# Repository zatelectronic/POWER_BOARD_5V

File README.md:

<div align="center">

# POWER BOARD +5V

**Placa de alimentação DC-DC step-down (buck converter) com entrada de 24V e saída regulada de 5V, baseada em regulador chaveado SMD de alta eficiência**

</div>

---

## 📋 Índice

- [POWER BOARD +5V](#power-board-5v)
  - [📋 Índice](#-índice)
  - [Visão Geral](#visão-geral)
  - [Renders 3D](#renders-3d)
  - [Funcionalidades](#funcionalidades)
  - [Diagrama de Funcionamento](#diagrama-de-funcionamento)
  - [Especificações Técnicas](#especificações-técnicas)
  - [Lista de Materiais](#lista-de-materiais)
  - [Pinagem dos Conectores](#pinagem-dos-conectores)
    - [DC IN — Entrada (lado esquerdo)](#dc-in--entrada-lado-esquerdo)
    - [DC OUT — Saída (lado direito)](#dc-out--saída-lado-direito)
    - [Pontos de Teste](#pontos-de-teste)
  - [Aplicações](#aplicações)
  - [Estrutura do Repositório](#estrutura-do-repositório)
  - [Como Usar](#como-usar)
    - [Instalação básica](#instalação-básica)
    - [Dica de Integração](#dica-de-integração)
  - [⚠️ Avisos de Segurança](#️-avisos-de-segurança)
  - [Sobre](#sobre)

---

## Visão Geral

**POWER BOARD +5V** é uma placa de alimentação DC-DC do tipo **buck converter (step-down)**, projetada pela **ZAT ELECTRONIC** utilizando **KiCad 10**. A placa converte uma tensão de entrada de **+24VDC** em uma saída regulada e estável de **+5VDC / 3A**, utilizando o regulador chaveado **LM2596S-5** no encapsulamento TO-263-5 (SMD).

O design é compacto e totalmente SMD, com conexões de entrada e saída por **pads de solda** expostos diretamente na PCB. A placa inclui **fusível de proteção SMD 3A**, **diodo Schottky** de roda livre, **indutor de 33µH** e capacitores eletrolíticos de alta capacidade para filtragem e estabilidade da saída.

> ⚡ Topologia **buck converter** de alta eficiência — ideal para sistemas embarcados, painéis de controle industrial e projetos que alimentam microcontroladores e periféricos a partir de fontes de 24VDC.

---

## Renders 3D

<div align="center">

*Vista superior — regulador LM2596S-5, indutor, capacitores eletrolíticos e fusível SMD*

<br/>

*Vista isométrica — layout compacto com pads DC IN e DC OUT nas extremidades*

</div>

---

## Funcionalidades

- ✅ **Regulador chaveado LM2596S-5** (TO-263-5 SMD) — saída fixa de 5V, até 3A
- ✅ **Topologia buck converter** — alta eficiência em comparação com reguladores lineares
- ✅ **Entrada 24VDC** — compatível com fontes industriais e painéis de automação
- ✅ **Saída 5VDC / 3A** — alimentação estável para microcontroladores e periféricos
- ✅ **Fusível SMD 3A** (encapsulamento 1808/2410) — proteção contra sobrecorrente na entrada
- ✅ **Diodo Schottky SS54** (SMA SMD) — diodo de roda livre de alta velocidade
- ✅ **Indutor 33µH** (12×12mm) — núcleo de potência para o estágio de conversão
- ✅ **Capacitor de entrada 100µF/35V** (SMD eletrolítico) — filtragem da tensão de entrada
- ✅ **Capacitor de saída 680µF/16V** (SMD eletrolítico) — filtragem e estabilidade da saída
- ✅ **4 pontos de teste (TP1–TP4)** — facilidade de medição e diagnóstico em bancada
- ✅ **Pads de conexão expostos** — DC IN (+24V / GND) e DC OUT (+5V / GND)
- ✅ **Layout totalmente SMD** — compacto e adequado para integração em painéis

---

## Diagrama de Funcionamento

```
DC IN (+24V) ──[F1 3A]──[D1 SMA]──────────────────────► +24V interno
                                   │
                                  [C5 100µF/35V] (filtro entrada)
                                   │
                              [U2 LM2596S-5]  ← Regulador buck
                                   │
                                  [L1 33µH]   ← Indutor de saída
                                   │
                    [D2 SS54] ←────┤            ← Diodo Schottky (roda livre)
                    (SMA SMD)      │
                                  [C6 680µF/16V] (filtro saída)
                                   │
DC OUT (+5V) ◄─────────────────────┘

DC IN (GND) ──────────────────────────────────────────► DC OUT (GND)

TP1, TP2 → pontos de teste na entrada
TP3, TP4 → pontos de teste na saída
```

---

## Especificações Técnicas

| Parâmetro | Valor |
|-----------|-------|
| **Topologia** | Buck Converter (Step-Down) |
| **Regulador** | LM2596S-5 (TO-263-5 SMD) |
| **Tensão de Entrada** | 24VDC |
| **Tensão de Saída** | 5VDC (fixa) |
| **Corrente de Saída máx.** | 3A |
| **Potência máxima de saída** | 15W |
| **Diodo de roda livre** | SS54 — Schottky 5A / 40V (SMA SMD) |
| **Indutor** | 33µH — 12×12×8mm |
| **Capacitor de entrada** | 100µF / 35V (eletrolítico SMD) |
| **Capacitor de saída** | 680µF / 16V (eletrolítico SMD) |
| **Fusível** | 3A (SMD 1808/2410) |
| **Pontos de teste** | 4x (TP1, TP2, TP3, TP4) |
| **Conexões** | Pads de solda expostos (DC IN / DC OUT) |
| **Ferramenta de Projeto** | KiCad 10 |
| **Tipo de montagem** | SMD |

---

## Lista de Materiais

| Ref | Componente | Valor / Parte | Encapsulamento |
|-----|-----------|--------------|----------------|
| U2 | Regulador Chaveado | LM2596S-5 | TO-263-5 SMD |
| L1 | Indutor de Potência | 33µH | 12×12×8mm |
| D2 | Diodo Schottky (roda livre) | SS54 — 5A / 40V | SMA SMD |
| D1 | Diodo SMD | SS36 | SMA SMD |
| C5 | Capacitor Eletrolítico (entrada) | 100µF / 35V | SMD Eletrolítico 10×10mm |
| C6 | Capacitor Eletrolítico (saída) | 680µF / 16V | SMD Eletrolítico 10×12,5mm |
| F1 | Fusível de Proteção | 3A | SMD 1808/2410 |
| TP1–TP4 | Pontos de Teste | — | SMD |

---

## Pinagem dos Conectores

A placa utiliza **pads de solda expostos** nas extremidades para conexão da entrada e saída. Não há conectores PTH — a ligação é feita diretamente por fios soldados ou trilhas de PCB mãe.

### DC IN — Entrada (lado esquerdo)

| Pad | Sinal | Descrição |
|-----|-------|-----------|
| + | +24V | Tensão de entrada positiva |
| − | GND | Terra / Negativo |

### DC OUT — Saída (lado direito)

| Pad | Sinal | Descrição |
|-----|-------|-----------|
| + | +5V | Tensão de saída regulada |
| − | GND | Terra / Negativo |

### Pontos de Teste

| Ref | Localização | Função |
|-----|-------------|--------|
| TP1 | Entrada | Medição +24V |
| TP2 | Entrada | Medição GND entrada |
| TP3 | Saída | Medição +5V |
| TP4 | Saída | Medição GND saída |

---

## Aplicações

- 🏭 **Automação industrial** — alimentação de CLPs, sensores e módulos a partir de barramentos 24V
- 🤖 **Projetos com Arduino e ESP32** — conversão de 24V industrial para 5V de lógica
- 💡 **Painéis de iluminação LED** — alimentação de controladoras a partir de fonte 24V
- 🔌 **Sistemas embarcados** — fonte embarcada compacta em projetos de hardware customizado
- 📡 **IoT industrial** — alimentação de gateways e módulos de comunicação
- 🖥️ **Painéis de controle** — fonte auxiliar de 5V integrada ao painel principal 24V

---

## Estrutura do Repositório

```
POWER_BOARD/
├── POWER_BOARD.kicad_pro         # Arquivo de projeto KiCad
├── POWER_BOARD.kicad_sch         # Esquemático (KiCad 10)
├── POWER_BOARD.kicad_pcb         # Layout da PCB (KiCad 10)
├── POWER_BOARD.kicad_prl         # Configurações locais do projeto
├── packages3D/                   # Modelos 3D arquivados (STEP / WRL)
│   ├── L_12x12mm_H8mm.step
│   ├── 1808-2410_Fuse.STEP
│   └── ...
├── fp-info-cache                 # Cache de footprints
├── imagem_1.png                  # Render 3D superior
├── imagem_2.png                  # Render 3D isométrico
└── README.md
```

---

## Como Usar

### Instalação básica

```
Fonte 24VDC (+) ────► Pad DC IN (+24V)
Fonte 24VDC (-) ────► Pad DC IN (GND)

Carga 5VDC      ────► Pad DC OUT (+5V)
Carga GND       ────► Pad DC OUT (GND)
```

### Dica de Integração

> 🔧 Para integração em PCB mãe, solde fios diretamente nos pads DC IN e DC OUT, ou projete a placa mãe com pads compatíveis para encaixe direto. Respeite a polaridade indicada na serigrafia (+24V / GND / +5V).

---

## ⚠️ Avisos de Segurança

> 🔴 **ATENÇÃO**

- **Não inverta a polaridade** na entrada — o fusível protege contra sobrecorrente, mas a inversão pode danificar o regulador.
- Respeite a **corrente máxima de 3A** na saída para não danificar o LM2596S-5.
- O regulador e o indutor podem **aquecer durante operação** em cargas próximas ao limite — garanta ventilação adequada.
- **Verifique a tensão de entrada** antes de conectar — tensões acima de 40V danificam o regulador.
- Utilize o **fusível SMD 3A** correto — nunca o substitua por um de valor superior sem analisar o circuito.

---

## Sobre

<div align="center">

Projetado por **ZAT ELECTRONIC**

*POWER BOARD +5V — Made in Brazil 🇧🇷*

</div>

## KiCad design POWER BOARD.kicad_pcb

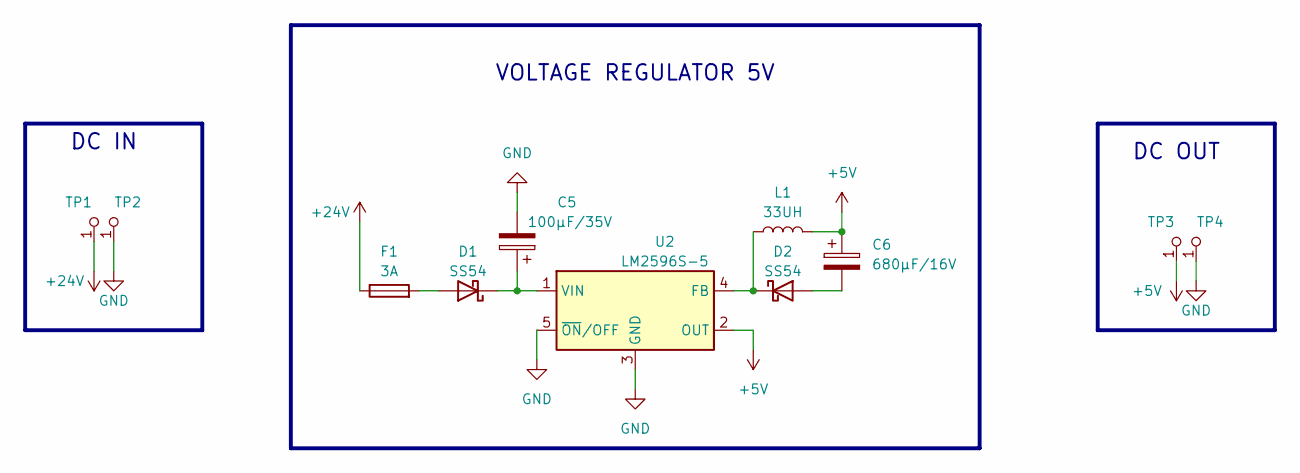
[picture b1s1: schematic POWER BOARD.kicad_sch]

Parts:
C5: 100μF/35V; CP_Elec_10x10
C6: 680μF/16V; CP_Elec_10x12.5
D1, D2: SS54; D_SMA
F1: 3A; Fuse_2010_5025Metric_Pad1.52x2.65mm_HandSolder
L1: 33UH; L_12x12mm_H8mm
TP1, TP2, TP3, TP4: S1751-46R; Test_Point_2.67x1.02mm; MPN S1751-46R; Digi-Key_PN 952-1478-1-ND
U2: LM2596S-5; TO-263-5_TabPin3

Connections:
+5V: C6.1, L1.1, TP3.1, U2.2 (OUT)
+24V: F1.1, TP1.1
GND: C5.2, TP2.1, TP4.1, U2.3 (GND), U2.5 (~ON/OFF)
unnamed: D1.2 (A), F1.2
unnamed: C5.1, D1.1 (K), U2.1 (VIN)
unnamed: C6.2, D2.2 (A)
unnamed: D2.1 (K), L1.2, U2.4 (FB)

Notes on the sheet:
DC OUT
DC IN
VOLTAGE REGULATOR 5V

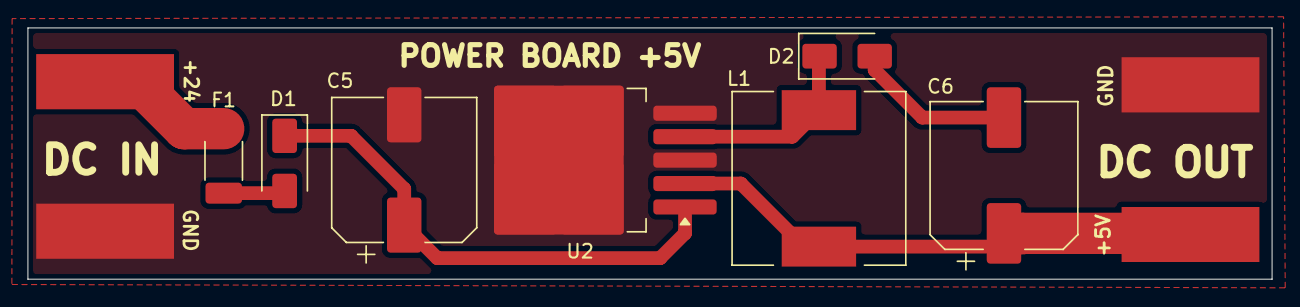
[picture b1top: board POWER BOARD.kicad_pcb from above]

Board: 2 copper layers, 90.3 x 18.2 mm, 11 parts (0 on the bottom side), 7 nets.

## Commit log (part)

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2026-06-28 commit_3
2026-06-29 COMMIT-4
